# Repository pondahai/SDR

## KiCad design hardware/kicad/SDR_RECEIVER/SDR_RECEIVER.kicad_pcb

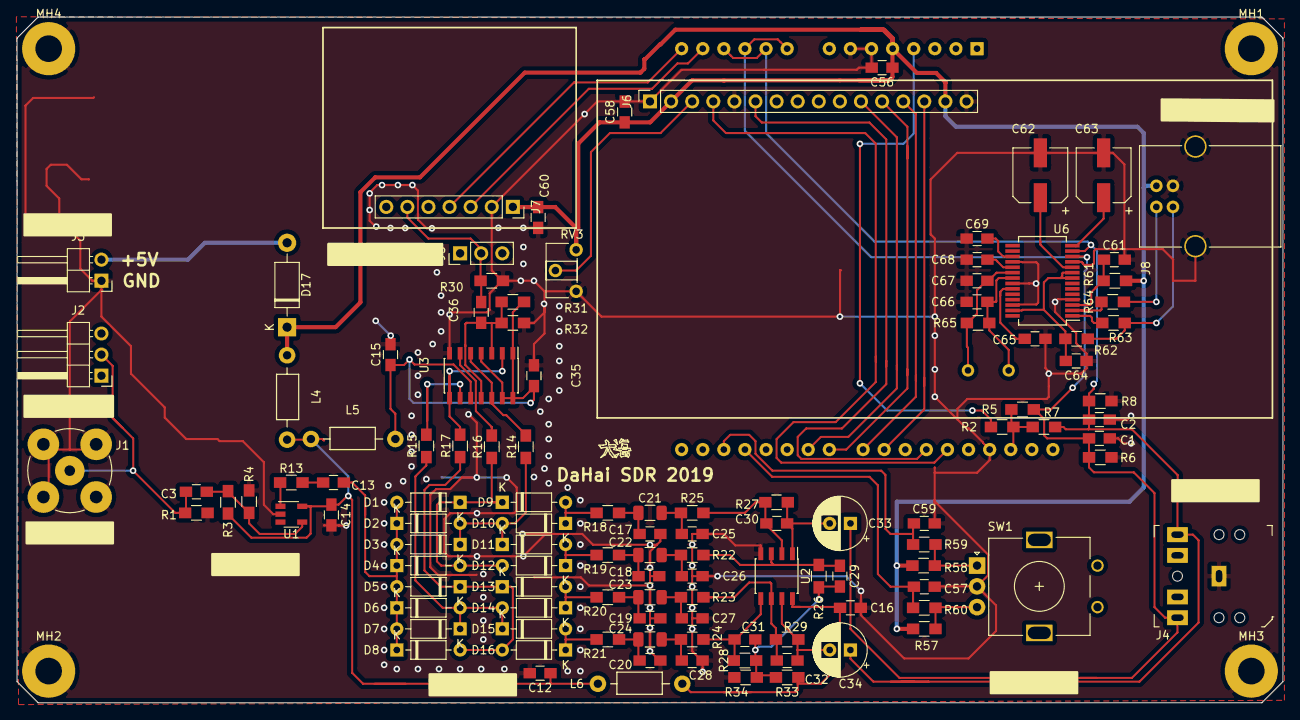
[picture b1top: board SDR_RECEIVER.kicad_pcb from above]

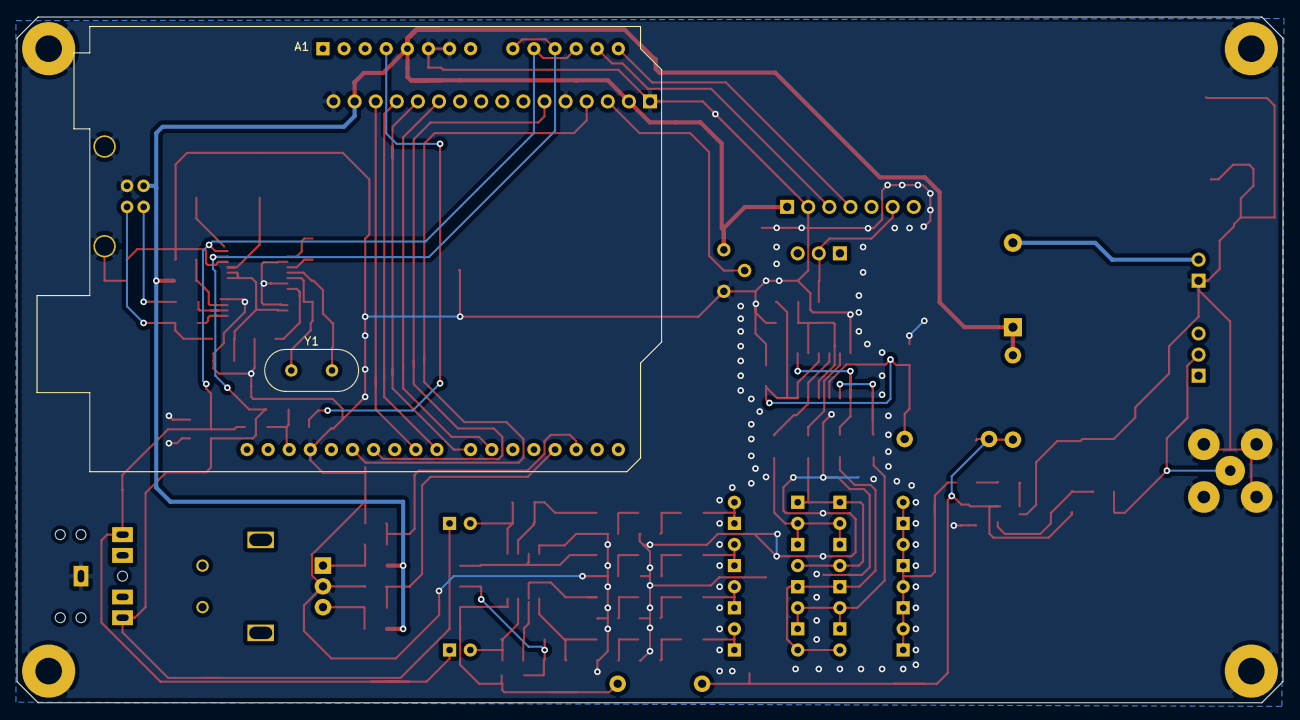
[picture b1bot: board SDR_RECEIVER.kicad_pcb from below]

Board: 2 copper layers, 152.4 x 82.6 mm, 121 parts (2 on the bottom side), 70 nets.

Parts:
A1: Arduino_UNO_R3
C1, C2, C57, C59: 10n; C_0805_HandSoldering
C3, C13, C14, C15, C16, C17, C18, C19, C20, C35, C36, C56, C58, C60: 100n; C_0805_HandSoldering
C12: 100u; C_0805_HandSoldering
C21, C22, C23, C24: 100n; C_1206_3216Metric
C25, C26, C27, C28: n/a; C_0805_HandSoldering
C29, C30, C31, C32: 56p; C_0805_HandSoldering
C33, C34: 22u; CP_Radial_D6.3mm_P2.50mm
C61, C64, C65, C68, C69: 1u; C_0805_HandSoldering
C62, C63: 10u; CP_Elec_6.3x4.5
C66, C67: 22p; C_0805_HandSoldering
D1, D2, D3, D4, D5, D6, D7, D8, D9, D10, D11, D12, D13, D14, D15, D16: 1N4148; D_DO-35_SOD27_P7.62mm_Horizontal
D17: 1N5819; D_DO-41_SOD81_P10.16mm_Horizontal
J1: ANT.; BNC_TEConnectivity_1478204_Vertical
J2: ANT.; Pin_Header_Angled_1x03_Pitch2.54mm
J3: POWER; Pin_Header_Angled_1x02_Pitch2.54mm
J4: IQ Output; audiojack-3.5mm-5p
J5: local osc; PinHeader_1x03_P2.54mm_Vertical
J6: LCM; PinSocket_1x16_P2.54mm_Vertical
J7: SI5351; PinSocket_1x07_P2.54mm_Vertical
J8: USB_B
L4: 330u; Choke_Horizontal_RM10mm
L5: 68u; Choke_Horizontal_RM10mm
L6: 1m; Choke_Horizontal_RM10mm
MH1, MH2, MH3, MH4: MountingHole_Pad; MountingHole_3.2mm_M3_Pad
R1, R13: 50; R_0805_HandSoldering
R2: 5k1; R_0805_HandSoldering
R3, R4, R22, R23, R24, R25, R31, R32, R57, R58, R59, R60: 10k; R_0805_HandSoldering
R5, R6, R7, R8, R26, R27, R28, R29: 100k; R_0805_HandSoldering
R14, R15, R16, R17: 680; R_0805_HandSoldering
R18, R19, R20, R21: 33; R_0805_HandSoldering
R30: 150; R_0805_HandSoldering
R33, R34: 1k; R_0805_HandSoldering
R61: 2.2; R_0805_HandSoldering
R62: 1.5k; R_0805_HandSoldering
R63, R64: 22; R_0805_HandSoldering
R65: 1M; R_0805_HandSoldering
RV3: 10k; Potentiometer_ACP_CA6-H2,5_Horizontal
SW1: Freq. Selector; RotaryEncoder_Alps_EC11E_Vertical_H20mm
U1: LMH6642/LMH6559(pin3 n.c.); TSOT-23-5
U2: LM358N; SOIC-8_3.9x4.9mm_P1.27mm
U3: 74ACT74; SOIC-14_3.9x8.7mm_P1.27mm
U6: PCM2902; SSOP-28_5.3x10.2mm_P0.65mm
Y1: 12MHz; Crystal_HC18-U_Vertical

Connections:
+3V3: A1.4, R2.1
+5V: A1.5, C56.1, C58.1, C60.1, D17.1, J6.2, J6.15, J7.1, J8.1, L4.1, R57.1, R58.1, R61.2, RV3.3
/4066receive/QaN: R16.2, U3.6
/4066receive/QaP: R14.2, U3.5, U3.12
/4066receive/QbN: R17.2, U3.2, U3.8
/4066receive/QbP: R15.2, U3.9
/4066receive/ant_in: C3.1, J1.1, J2.2, R1.1
/arduino/A0: A1.9, A1.11, C1.1, C33.1, J4.R, R5.2, R6.1, U6.12
/arduino/A1: A1.10, A1.12, C2.1, C34.1, J4.T, R7.2, R8.1, U6.13
/arduino/AREF: A1.30, R2.2, R5.1, R7.1
/arduino/CLK_OUT: C36.2, J5.2, J7.6, R30.2
GND: A1.6, A1.7, A1.29, C1.2, C2.2, C12.2, C14.2, C15.2, C16.2, C17.2, C18.2, C19.2, C20.2, C25.2, C26.2, C27.2, C28.2, C35.1, C56.2, C57.2, C58.2, C59.2, C60.2, C61.2, C62.2, C63.2, C64.1, C65.1, C66.1, C67.1, C68.1, C69.1, J1.2, J3.1, J4.S, J6.1, J6.5, J6.16, J7.2, J8.4, J8.5, MH1.1, MH2.1, MH3.1, MH4.1, R1.2, R4.2, R6.2, R8.2, R30.1, R32.1, R34.1, RV3.1, SW1.C, U1.2, U2.4, U3.7, U6.4, U6.11, U6.18, U6.22, U6.26
unnamed: A1.13, J7.3
unnamed: A1.14, J7.4
unnamed: A1.17, C59.1, R59.2
unnamed: A1.18, C57.1, R60.2
unnamed: A1.21, J6.11
unnamed: A1.22, J6.12
unnamed: A1.23, J6.13
unnamed: A1.24, J6.14
unnamed: A1.26, J6.6
unnamed: A1.27, J6.4
unnamed: C3.2, R3.2, R4.1, U1.4
unnamed: C13.1, R13.2
unnamed: C13.2, D1.2, D2.1, D3.2, D4.1, D5.2, D6.1, D7.2, D8.1
unnamed: C17.1, C21.2, R18.1
unnamed: C18.1, C22.2, R19.1
unnamed: C19.1, C23.2, R20.1
unnamed: C20.1, C24.2, R21.1
unnamed: C21.1, C25.1, R25.2
unnamed: C22.1, C26.1, R22.2
unnamed: C23.1, C27.1, R23.2
unnamed: C24.1, C28.1, R24.2
unnamed: C29.1, C31.1, R26.1, R28.1, R33.1, R34.2
unnamed: C29.2, R22.1, R26.2, U2.3
unnamed: C30.1, C33.2, R27.1, U2.1
unnamed: C30.2, R25.1, R27.2, U2.2
unnamed: C31.2, R24.1, R28.2, U2.5
unnamed: C32.1, C34.2, R29.1, U2.7
unnamed: C32.2, R23.1, R29.2, U2.6
unnamed: C36.1, R31.1, R32.2, U3.3, U3.11
unnamed: C61.1, R61.1, U6.3
unnamed: C62.1, U6.10
unnamed: C63.1, U6.14
unnamed: C64.2, R62.2, U6.8, U6.9, U6.27
unnamed: C65.2, U6.23
unnamed: C66.2, R65.2, U6.21, Y1.1
unnamed: C67.2, R65.1, U6.20, Y1.2
unnamed: C68.2, U6.19
unnamed: C69.2, U6.17
unnamed: D1.1, D4.2, D9.1, D12.2, R16.1
unnamed: D9.2, D10.1, R18.2
unnamed: D2.2, D3.1, D10.2, D11.1, R14.1
unnamed: D11.2, D12.1, R19.2
unnamed: D5.1, D8.2, D13.1, D16.2, R17.1
unnamed: D13.2, D14.1, R20.2
unnamed: D6.2, D7.1, D14.2, D15.1, R15.1
unnamed: D15.2, D16.1, R21.2
unnamed: D17.2, J3.2
unnamed: J6.3, RV3.2
unnamed: J8.2, R64.2
unnamed: J8.3, R62.1, R63.2
unnamed: R13.1, U1.1
unnamed: R57.2, R60.1, SW1.B
unnamed: R58.2, R59.1, SW1.A
unnamed: R63.1, U6.1
unnamed: R64.1, U6.2
VCC: C15.1, C35.2, L5.2, R31.2, U3.1, U3.4, U3.10, U3.13, U3.14
VDD: C12.1, C14.1, L4.2, L5.1, L6.1, R3.1, U1.5
VPP: C16.1, L6.2, R33.2, U2.8

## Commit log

2019-08-18 init
2019-08-21 ppt update
